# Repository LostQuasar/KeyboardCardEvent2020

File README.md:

# Keyboard Business Card Event 2020
How to sumbit your card!

First you will want to fork this repository. Then you will want to create a subfolder with your username in the submission folder of this repository. 

IE: 

    submissions
      └───username

In that folder upload:
- 1 or more pictures of your completed build
- if using KiCad, if not upload source files for appropriate program
  - `card name`.kicad_pcb 
  - `card name`.pro 
  - `card name`.sch
- `card name`.zip (a zip of the Gerber files)
- readme.md containing info from the [template](/template/readme.md)
- an edited version of `LICENSE` containing your name or username
- please host images on imgur instead of putting them in the repo

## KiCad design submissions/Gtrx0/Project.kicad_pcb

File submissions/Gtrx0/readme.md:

Business card made by Gtrx

# Concept
A modern, sleek and usable business card with an NFC tag, QR code and the ability to open a website/copy text to clipboard once plugged into a computer.

# Description
The card uses an IC that acts as an NFC tag (M24LR04E-R) which can be scanned by any NFC compatible device. After scanning, the device opens the website (Gtrxengineering.com). The NFC tag can work without the board being powered. Once the board is plugged into a computer, one of the 2 switches can be pressed. Depending on which switch is pressed, either the website will open or the email address will be copied to clipboard. The QR code also opens the website.

The website and email aren't "real" yet :P.

Thanks for reading!

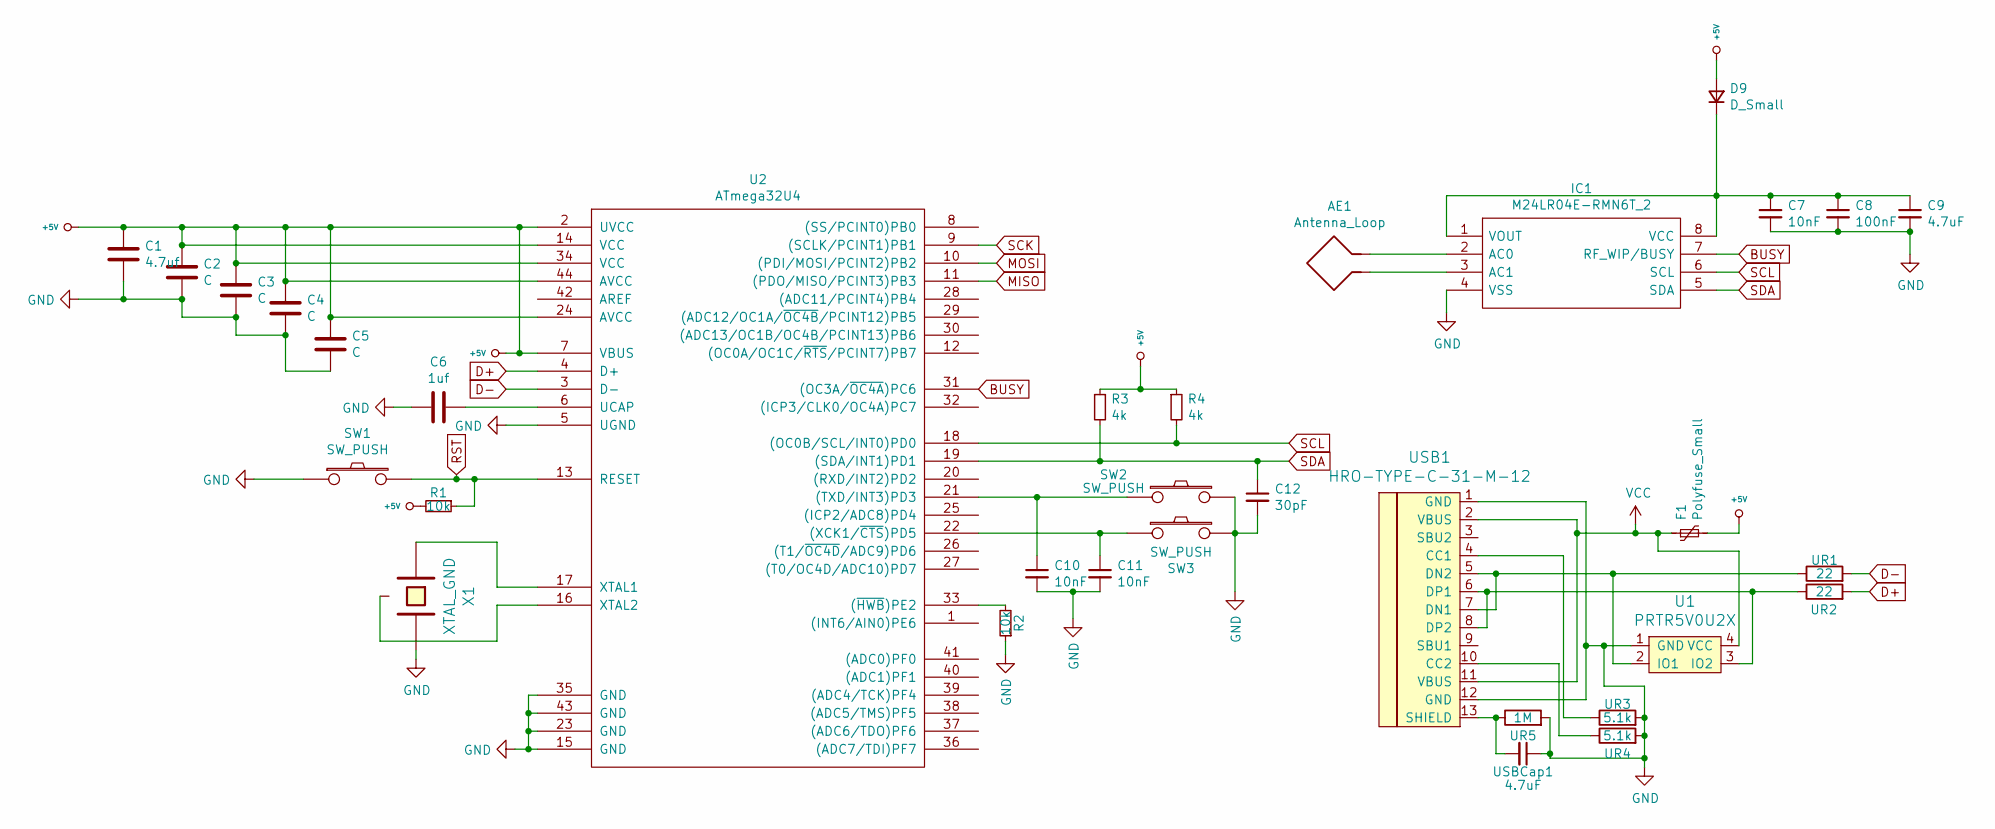
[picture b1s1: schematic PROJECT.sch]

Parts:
AE1: Antenna_Loop
C1: 4.7uf; C_0603_1608Metric
C2, C3, C4, C5: C; C_0603_1608Metric
C6: 1uf; C_0603_1608Metric
C7, C10, C11: 10nF; C_0603_1608Metric
C8: 100nF; C_0603_1608Metric
C9: 4.7uF; C_0603_1608Metric
C12: 30pF; C_0603_1608Metric
D9: D_Small; D_SOD-123
F1: Polyfuse_Small; Fuse_0805_2012Metric
IC1: M24LR04E-RMN6T_2; SOIC127P600X175-8N; Mouser Part Number 511-M24LR04E-RMN6T/2
R1, R2: 10k; R_0603_1608Metric
R3, R4: 4k; R_0603_1608Metric
SW1, SW2, SW3: SW_PUSH; SW_SPST_TL3342
U1: PRTR5V0U2X; SOT143B
U2: ATmega32U4; QFN-44-1EP_7x7mm_P0.5mm_EP5.2x5.2mm_ThermalVias
UR1, UR2: 22; R_0603_1608Metric
UR3, UR4: 5.1k; R_0603_1608Metric
UR5: 1M; R_0603_1608Metric
USB1: HRO-TYPE-C-31-M-12; HRO-TYPE-C-31-M-13
USBCap1: 4.7uF; C_0603_1608Metric
X1: XTAL_GND; CSTCE

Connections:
+5V: C1.1, C2.1, C3.1, C4.1, C5.1, D9.2 (A), F1.2, R1.2, R3.1, R4.1, U2.2 (UVCC), U2.7 (VBUS), U2.14 (VCC), U2.24 (AVCC), U2.34 (VCC), U2.44 (AVCC)
BUSY: IC1.7 (RF_WIP/BUSY), U2.31 ((OC3A/~OC4A~)PC6)
D+: U2.4 (D+), UR2.2
D-: U2.3 (D-), UR1.2
GND: C1.2, C2.2, C3.2, C4.2, C5.2, C6.2, C7.2, C8.2, C9.2, C10.2, C11.2, C12.2, IC1.4 (VSS), R2.1, SW1.1, SW2.2, SW3.2, U1.1 (GND), U2.5 (UGND), U2.15 (GND), U2.23 (GND), U2.35 (GND), U2.43 (GND), U2.45, UR3.2, UR4.2, UR5.2, USB1.1 (GND), USB1.12 (GND), USBCap1.1, X1.2; also elsewhere on the board
MISO: U2.11 ((PDO/MISO/PCINT3)PB3)
MOSI: U2.10 ((PDI/MOSI/PCINT2)PB2)
unnamed: AE1.1, AE1.2, IC1.2 (AC0), IC1.3 (AC1)
unnamed: C6.1, U2.6 (UCAP)
unnamed: C7.1, C8.1, C9.1, D9.1 (K), IC1.1 (VOUT), IC1.8 (VCC)
unnamed: C10.1, SW2.1, U2.21 ((TXD/INT3)PD3)
unnamed: C11.1, SW3.1, U2.22 ((XCK1/~CTS~)PD5)
unnamed: R2.2, U2.33 ((~HWB~)PE2)
unnamed: U1.2 (IO1), UR1.1, USB1.5 (DN2), USB1.7 (DN1)
unnamed: U1.3 (IO2), UR2.1, USB1.6 (DP1), USB1.8 (DP2)
unnamed: U2.16 (XTAL2), X1.3
unnamed: U2.17 (XTAL1), X1.1
unnamed: UR3.1, USB1.4 (CC1)
unnamed: UR4.1, USB1.10 (CC2)
unnamed 37: UR5.1, USB1.13 (SHIELD), USBCap1.2; also elsewhere on the board
RST: R1.1, SW1.2, U2.13 (RESET); also elsewhere on the board
SCK: U2.9 ((SCLK/PCINT1)PB1)
SCL: IC1.6 (SCL), R4.2, U2.18 ((OC0B/SCL/INT0)PD0)
SDA: C12.1, IC1.5 (SDA), R3.2, U2.19 ((SDA/INT1)PD1)
VCC: F1.1, U1.4 (VCC), USB1.2 (VBUS), USB1.11 (VBUS)

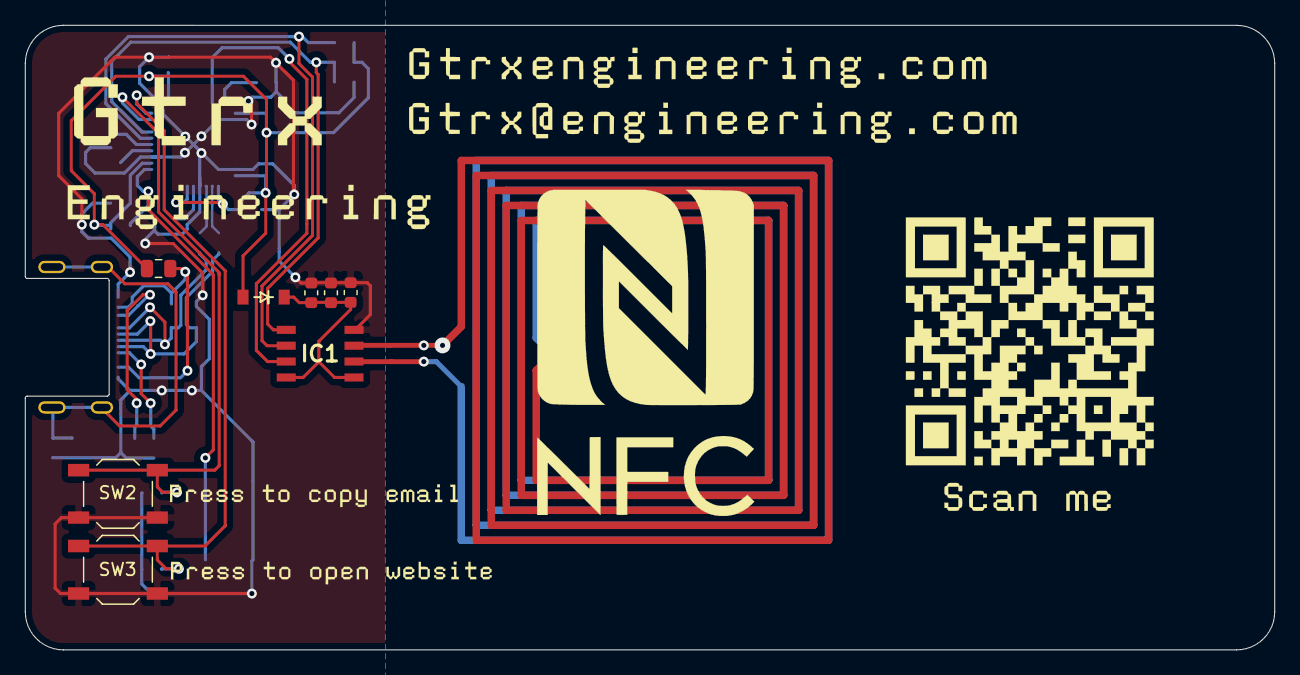
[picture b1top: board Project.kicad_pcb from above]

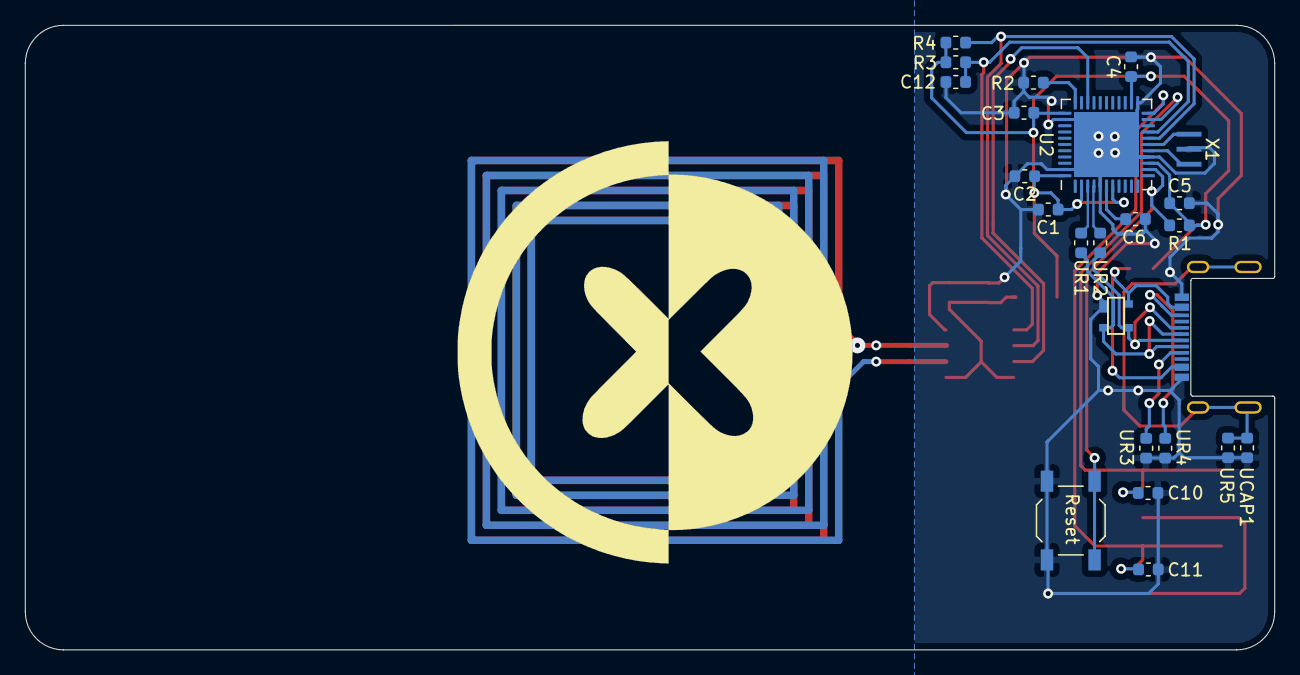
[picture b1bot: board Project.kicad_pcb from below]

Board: 2 copper layers, 100.0 x 50.0 mm, 32 parts (24 on the bottom side), 22 nets.

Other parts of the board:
Reset: SW_PUSH; SW_SPST_TL3342
UCAP1: 4.7uF; C_0603_1608Metric

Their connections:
GND: Reset.1, UCAP1.1; also elsewhere on the board
unnamed 37: UCAP1.2; also elsewhere on the board
RST: Reset.2; also elsewhere on the board

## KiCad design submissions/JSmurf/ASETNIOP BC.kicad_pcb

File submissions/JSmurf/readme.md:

# JSmurf's Business Card

## [Currently Untitled Keyboard]

[Currently Untitled Keyboard] is a one-handed ASETNIOP keyboard that is designed to be a fully-featured keyboard.

(More information to follow as development continues.)

## Parts list

- 1x ATMEGA32U4 Microcontroller
- 1x Crystal, 16MHz
- 1x Mini-B USB Connector Molex-0548190589
- 1x Low Profile Tactile Switch
- 2x Resistor, 22ohm SMD 0805
- 2x Resistor, 10k SMD 0805
- 1x Capacitor, 1uF SMD 0805
- 1x Capacitor, 10uF SMD 0805
- 3x Capacitor, 0.1uF SMD 0805
- 2x Capacitor, 22pF SMD 0805
- 10x Diode, SMD SOD-123
- 1x Polyfuse, 500mA hold, 1A trip
- 10x MX Keyswitches of your choice

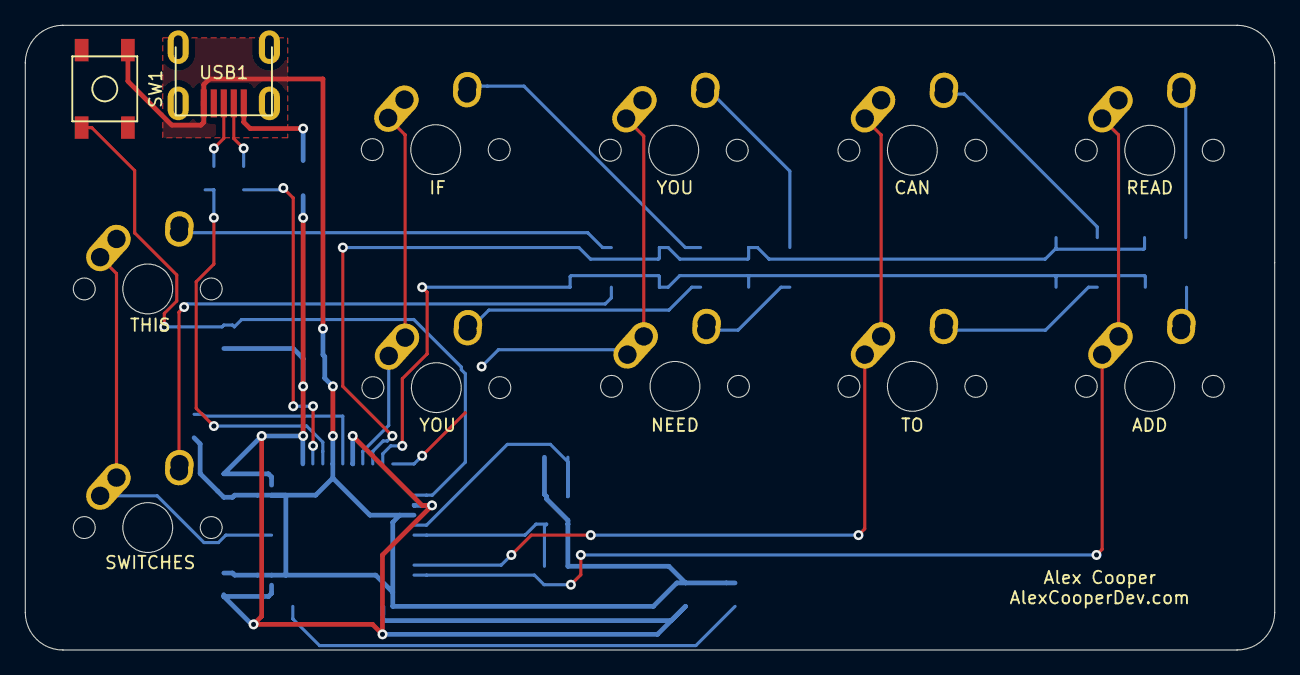
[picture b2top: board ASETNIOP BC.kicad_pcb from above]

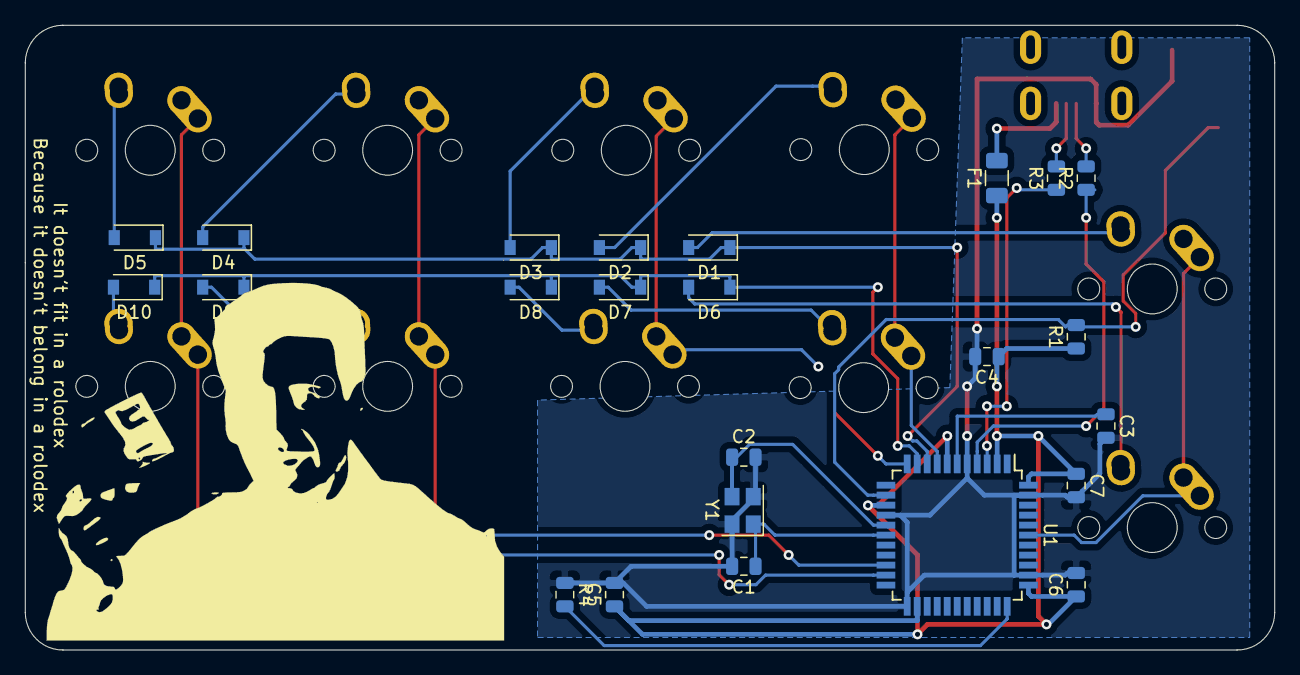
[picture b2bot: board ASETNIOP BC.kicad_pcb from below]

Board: 2 copper layers, 100.0 x 50.0 mm, 36 parts (24 on the bottom side), 29 nets.

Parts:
C1, C2: 22pF; C_0805_2012Metric
C3: 1uF; C_0805_2012Metric
C4, C5, C6: 0.1uF; C_0805_2012Metric
C7: 10uF; C_0805_2012Metric
D1, D2, D3, D4, D5, D6, D7, D8, D9, D10: SOD-123; D_SOD-123
F1: 500mA; Fuse_1206_3216Metric
MX1, MX2, MX3, MX4, MX5, MX6, MX7, MX8, MX9, MX10: MX-NoLED; MX-1U-NoLED
R1, R4: 10k; R_0805_2012Metric
R2, R3: 22; R_0805_2012Metric
SW1: SW_Push; SKQG-1155865
U1: ATmega32U4-AU; TQFP-44_10x10mm_P0.8mm
USB1: Molex-0548190589
Y1: 16MHz; Crystal_SMD_3225-4Pin_3.2x2.5mm

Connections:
+5V: C4.1, C5.1, C6.1, C7.1, F1.1, R1.1, U1.2, U1.7, U1.14, U1.24, U1.34, U1.44
COL0: MX1.1, MX6.1, U1.39
COL1: MX2.1, MX7.1, U1.8
COL2: MX3.1, MX8.1, U1.11
COL3: MX4.1, MX9.1, U1.20
COL4: MX5.1, MX10.1, U1.21
D+: R2.2, USB1.3
D-: R3.2, USB1.4
GND: C1.2, C2.2, C3.2, C4.2, C5.2, C6.2, C7.2, R4.1, SW1.1, U1.5, U1.15, U1.23, U1.35, U1.43, USB1.1, Y1.2, Y1.4
unnamed: C1.1, U1.17, Y1.1
unnamed: C2.1, U1.16, Y1.3
unnamed: C3.1, U1.6
unnamed: D1.2, MX1.2
unnamed: D2.2, MX2.2
unnamed: D3.2, MX3.2
unnamed: D4.2, MX4.2
unnamed: D5.2, MX5.2
unnamed: D6.2, MX6.2
unnamed: D7.2, MX7.2
unnamed: D8.2, MX8.2
unnamed: D9.2, MX9.2
unnamed: D10.2, MX10.2
unnamed: R1.2, SW1.2, U1.13
unnamed: R2.1, U1.4
unnamed: R3.1, U1.3
unnamed: R4.2, U1.33
ROW0: D1.1, D2.1, D3.1, D4.1, D5.1, U1.9
ROW1: D6.1, D7.1, D8.1, D9.1, D10.1, U1.10
VCC: F1.2, USB1.5

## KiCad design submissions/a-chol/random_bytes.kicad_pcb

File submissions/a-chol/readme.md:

# random_bytes' Business card

Here is a business card which functionality is related to my username.

The feature of the card is to generate random outputs where the source of randomness is a hardware random number generator, just by pressing the capacitive touch area on the card.

The hardware random number generator is based on [the following article](https://makezine.com/projects/really-really-random-number-generator/) with its implementation in the RAND frame on the card.

For this to work, I needed a 18V power source, so I implemented a 5V to 18V step up in the POWER frame.

The DIP switches let the user chose between different output formats, which could be 8bit integer, floating point value, alphanumeric keystrokes, mouse pointer displacement, ...

The USB-C port is a concept experiment where the connector plate of a USB-C receptacle is built in the PCB. If the PCB is printed with 0.6mm width, this could work.

I have no idea if it works!

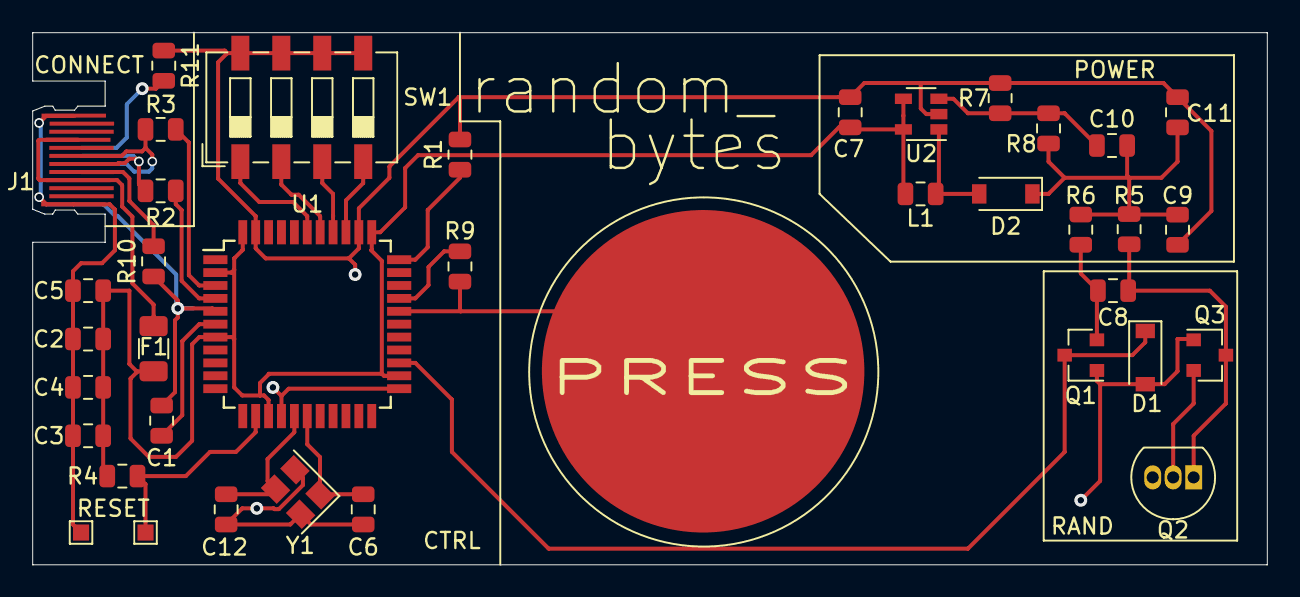
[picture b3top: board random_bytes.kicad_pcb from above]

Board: 2 copper layers, 76.6 x 33.0 mm, 38 parts (0 on the bottom side), 27 nets.

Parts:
C1: 1uF; C_0805_2012Metric
C2, C3, C4: 0.1uF; C_0805_2012Metric
C5: 10uF; C_0805_2012Metric
C6, C10, C12: 22pF; C_0805_2012Metric
C7: 4.7µF; C_0805_2012Metric
C8, C9: 0.01uF; C_0805_2012Metric
C11: 1µF; C_0805_2012Metric
CapSensor1: Capacitive_circular_pad
D1: D_Zener_Small; D_SOD-123
D2: D_Schottky; D_SOD-123
F1: Polyfuse_Small; Fuse_1206_3216Metric
GND_Pad1: TestPoint; TestPoint_Pad_1.0x1.0mm
J1: USB_C_Receptacle; USB-C_onboard_pins
L1: 10µH; L_0805_2012Metric
Q1, Q3: MMBT3904; SOT-23
Q2: 2N3904; TO-92_Inline
R1, R4: 10k; R_0805_2012Metric
R2, R3: 22; R_0805_2012Metric
R5: 4.7k; R_0805_2012Metric
R6, R9: 1M; R_0805_2012Metric
R7: 160k; R_0805_2012Metric
R8: 2.2M; R_0805_2012Metric
R10, R11: 5.1k; R_0805_2012Metric
RST_Pad1: TestPoint; TestPoint_Pad_1.0x1.0mm
SW1: SW_DIP_x04; SW_DIP_SPSTx04_Slide_6.7x11.72mm_W6.73mm_P2.54mm_LowProfile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
U1: ATmega32U4-AU; TQFP-44_10x10mm_P0.8mm
U2: TPS61041DBV; SOT-23-5
Y1: 16MHz; Crystal_SMD_3225-4Pin_3.2x2.5mm

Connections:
18V: C9.2, C10.2, C11.2, D2.1, R5.2, R6.2, R8.1
+5V: C2.1, C3.1, C4.1, C5.1, C7.2, F1.1, L1.2, R4.2, U1.2, U1.7, U1.14, U1.24, U1.34, U1.44, U2.4, U2.5
CAP_POWER: CapSensor1.1, R9.1, U1.29
CAP_VAL: R9.2, U1.30
D+: J1.A6, J1.B6, R2.2
D-: J1.A7, J1.B7, R3.2
GND: C1.2, C2.2, C3.2, C4.2, C5.2, C6.2, C7.1, C9.1, C11.1, C12.2, D1.2, GND_Pad1.1, J1.A1, J1.A12, J1.B1, J1.B12, Q1.1, Q3.1, R1.2, R7.2, R10.1, R11.1, SW1.5, SW1.6, SW1.7, SW1.8, U1.5, U1.15, U1.23, U1.35, U1.43, U2.2, Y1.2, Y1.4
unnamed: C1.1, U1.6
unnamed: C6.1, U1.17, Y1.1
unnamed: C8.1, Q2.1, Q3.3, R5.1
unnamed: C8.2, Q1.2, R6.1
unnamed: C10.1, R7.1, R8.2, U2.3
unnamed: C12.1, U1.16, Y1.3
unnamed: D2.2, L1.1, U2.1
unnamed: J1.A5, R10.2
unnamed: J1.B5, R11.2
unnamed: Q2.2, Q3.2
unnamed: R1.1, U1.33
unnamed: R2.1, U1.4
unnamed: R3.1, U1.3
unnamed: R4.1, RST_Pad1.1, U1.13
unnamed: SW1.1, U1.39
unnamed: SW1.2, U1.38
unnamed: SW1.3, U1.37
unnamed: SW1.4, U1.36
RAND: D1.1, Q1.3, U1.25
VCC: F1.2, J1.A4, J1.A9, J1.B4, J1.B9

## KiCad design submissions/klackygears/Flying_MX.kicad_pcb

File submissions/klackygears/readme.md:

# klackygears's Business card

This is my first pcb design. (I followed ai03's guide. Huge thank you!) I thought it would be fun to try some things while I was learning. It has footprints for SK6812 MINI-E that I hope work. (Big thanks to Maarten for making 95% of that footprint!) It also has a fun silk screen design I made that is inspired by the old Flying Toaster screensaver.

It's a 6 key macro pad with per-key RGB and USB C connector.

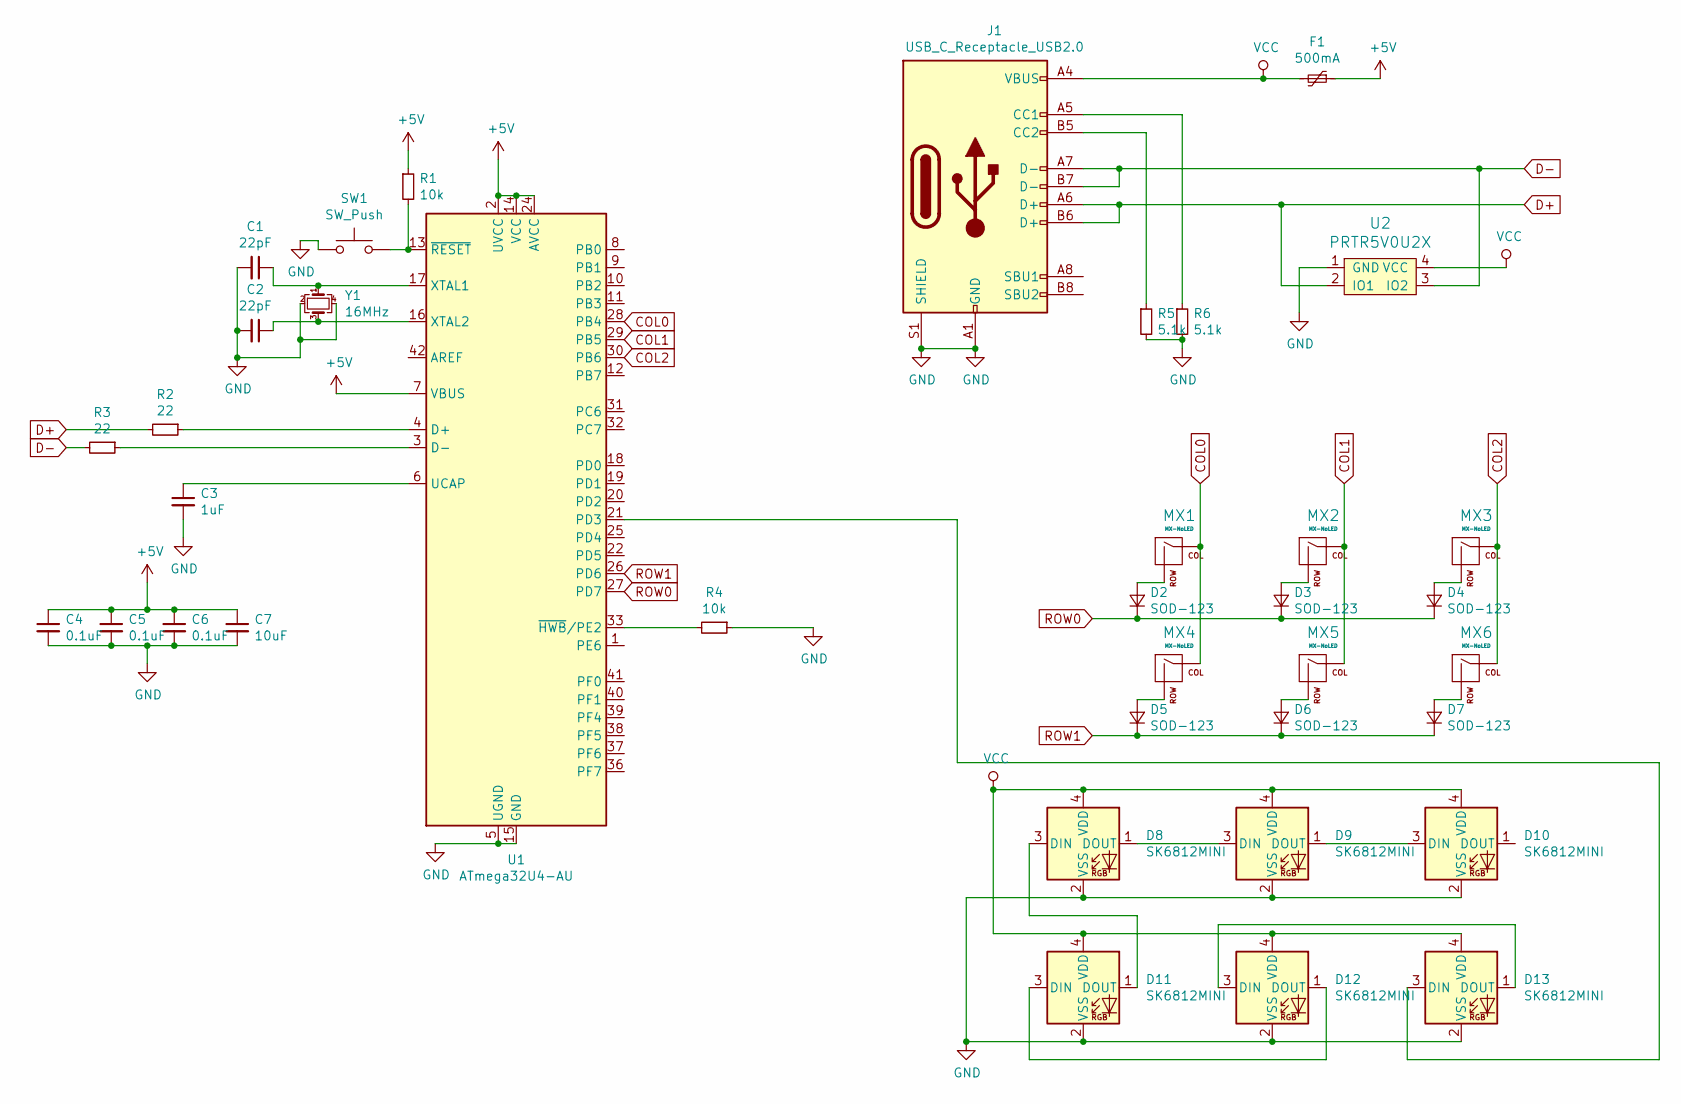
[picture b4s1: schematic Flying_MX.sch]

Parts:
C1, C2: 22pF; C_0805_2012Metric
C3: 1uF; C_0805_2012Metric
C4, C5, C6: 0.1uF; C_0805_2012Metric
C7: 10uF; C_0805_2012Metric
D2, D3, D4, D5, D6, D7: SOD-123; D_SOD-123
D8, D9, D10, D11, D12, D13: SK6812MINI; SK6812MINI-E
F1: 500mA; Fuse_1206_3216Metric
J1: USB_C_Receptacle_USB2.0; USB_C_Receptacle_GCT_USB4085
MX1, MX2, MX3, MX4, MX5, MX6: MX-NoLED; MX-ALPs-PG1350-FLIP
R1, R4: 10k; R_0805_2012Metric
R2, R3: 22; R_0805_2012Metric
R5, R6: 5.1k; R_0805_2012Metric
SW1: SW_Push; SKQG-1155865
U1: ATmega32U4-AU; TQFP-44_10x10mm_P0.8mm
U2: PRTR5V0U2X; SOT143B
Y1: 16MHz; Crystal_SMD_3225-4Pin_3.2x2.5mm

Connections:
+5V: C4.1, C5.1, C6.1, C7.1, F1.1, R1.1, U1.2 (UVCC), U1.7 (VBUS), U1.14 (VCC), U1.24 (AVCC), U1.34 (VCC), U1.44 (AVCC)
COL0: MX1.1 (COL), MX4.1 (COL), U1.28 (PB4)
COL1: MX2.1 (COL), MX5.1 (COL), U1.29 (PB5)
COL2: MX3.1 (COL), MX6.1 (COL), U1.30 (PB6)
D+: J1.A6 (D+), J1.B6 (D+), R2.2, U2.2 (IO1)
D-: J1.A7 (D-), J1.B7 (D-), R3.2, U2.3 (IO2)
GND: C1.2, C2.2, C3.2, C4.2, C5.2, C6.2, C7.2, D8.2 (VSS), D9.2 (VSS), D10.2 (VSS), D11.2 (VSS), D12.2 (VSS), D13.2 (VSS), J1.A1 (GND), J1.A12 (GND), J1.B1 (GND), J1.B12 (GND), J1.S1 (SHIELD), R4.1, R5.2, R6.2, SW1.1, U1.5 (UGND), U1.15 (GND), U1.23 (GND), U1.35 (GND), U1.43 (GND), U2.1 (GND), Y1.2, Y1.4
unnamed: C1.1, U1.17 (XTAL1), Y1.1
unnamed: C2.1, U1.16 (XTAL2), Y1.3
unnamed: C3.1, U1.6 (UCAP)
unnamed: D2.2 (A), MX1.2 (ROW)
unnamed: D3.2 (A), MX2.2 (ROW)
unnamed: D4.2 (A), MX3.2 (ROW)
unnamed: D5.2 (A), MX4.2 (ROW)
unnamed: D6.2 (A), MX5.2 (ROW)
unnamed: D7.2 (A), MX6.2 (ROW)
unnamed: D8.1 (DOUT), D9.3 (DIN)
unnamed: D9.1 (DOUT), D10.3 (DIN)
unnamed: D8.3 (DIN), D11.1 (DOUT)
unnamed: D11.3 (DIN), D12.1 (DOUT)
unnamed: D12.3 (DIN), D13.1 (DOUT)
unnamed: D13.3 (DIN), U1.21 (PD3)
unnamed: J1.A5 (CC1), R6.1
unnamed: J1.B5 (CC2), R5.1
unnamed: R1.2, SW1.2, U1.13 (~RESET)
unnamed: R2.1, U1.4 (D+)
unnamed: R3.1, U1.3 (D-)
unnamed: R4.2, U1.33 (~HWB~/PE2)
ROW0: D2.1 (K), D3.1 (K), D4.1 (K), U1.27 (PD7)
ROW1: D5.1 (K), D6.1 (K), D7.1 (K), U1.26 (PD6)
VCC: D8.4 (VDD), D9.4 (VDD), D10.4 (VDD), D11.4 (VDD), D12.4 (VDD), D13.4 (VDD), F1.2, J1.A4 (VBUS), J1.A9 (VBUS), J1.B4 (VBUS), J1.B9 (VBUS), U2.4 (VCC)

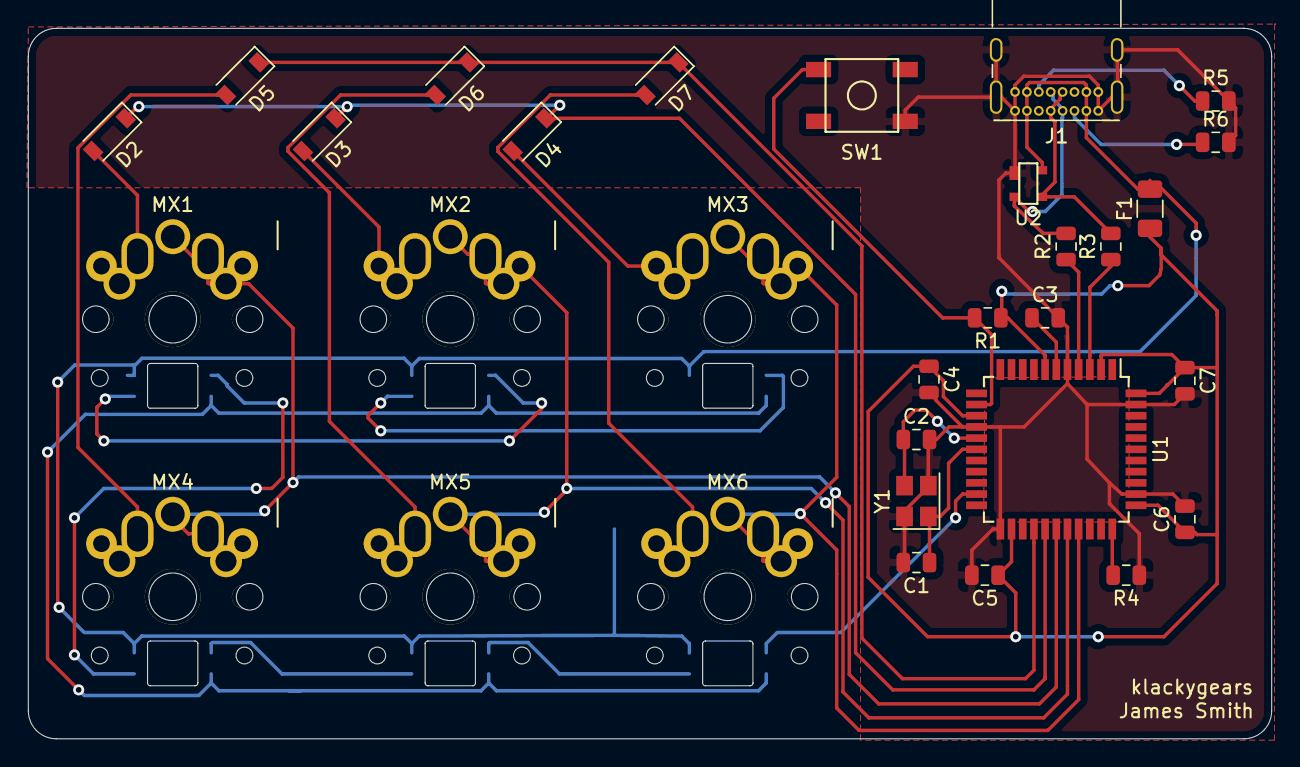
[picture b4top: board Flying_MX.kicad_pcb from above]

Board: 2 copper layers, 88.9 x 50.8 mm, 37 parts (0 on the bottom side), 31 nets.

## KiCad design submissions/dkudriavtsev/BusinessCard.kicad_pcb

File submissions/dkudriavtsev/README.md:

# dkudriavtsev's submission

This is a Planck-like keyboard in a 100x50mm form factor. It can be manufactured entirely through JLCPCB.

Features include full N-key rollover, STM32 ARM microcontroller, USB-C, ESD protection, and more.

Compatible with QMK firmware.

## Images

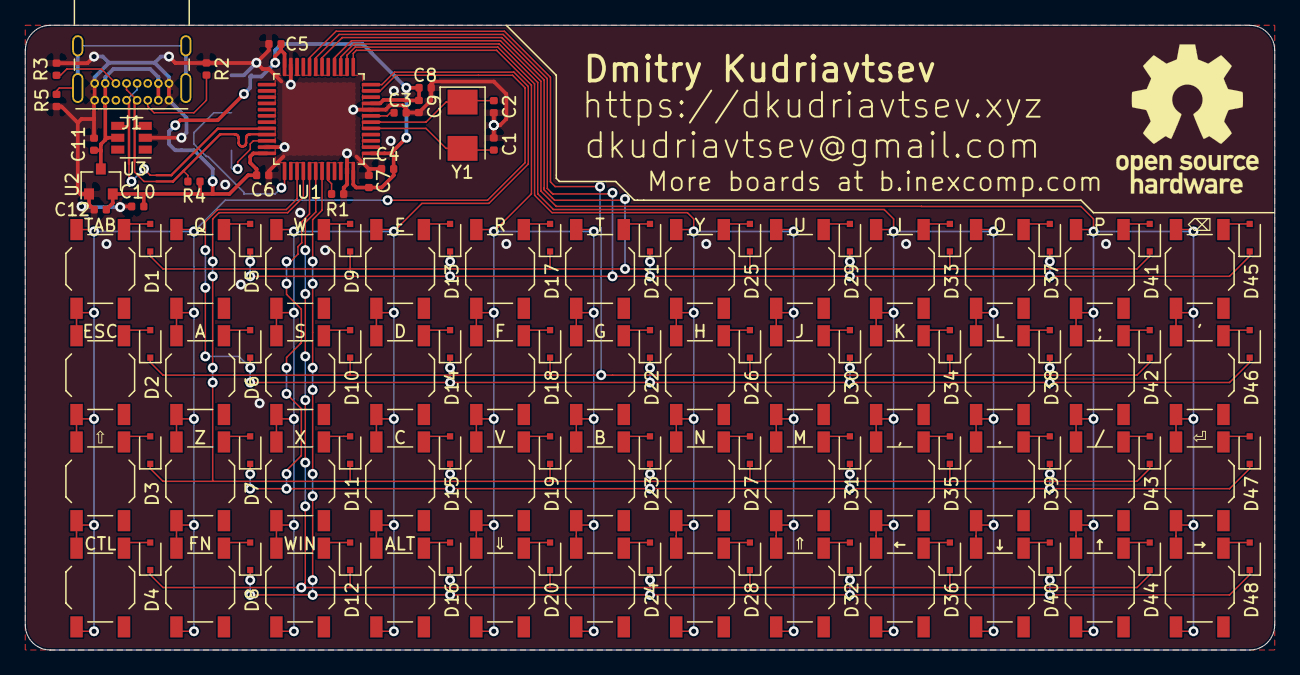
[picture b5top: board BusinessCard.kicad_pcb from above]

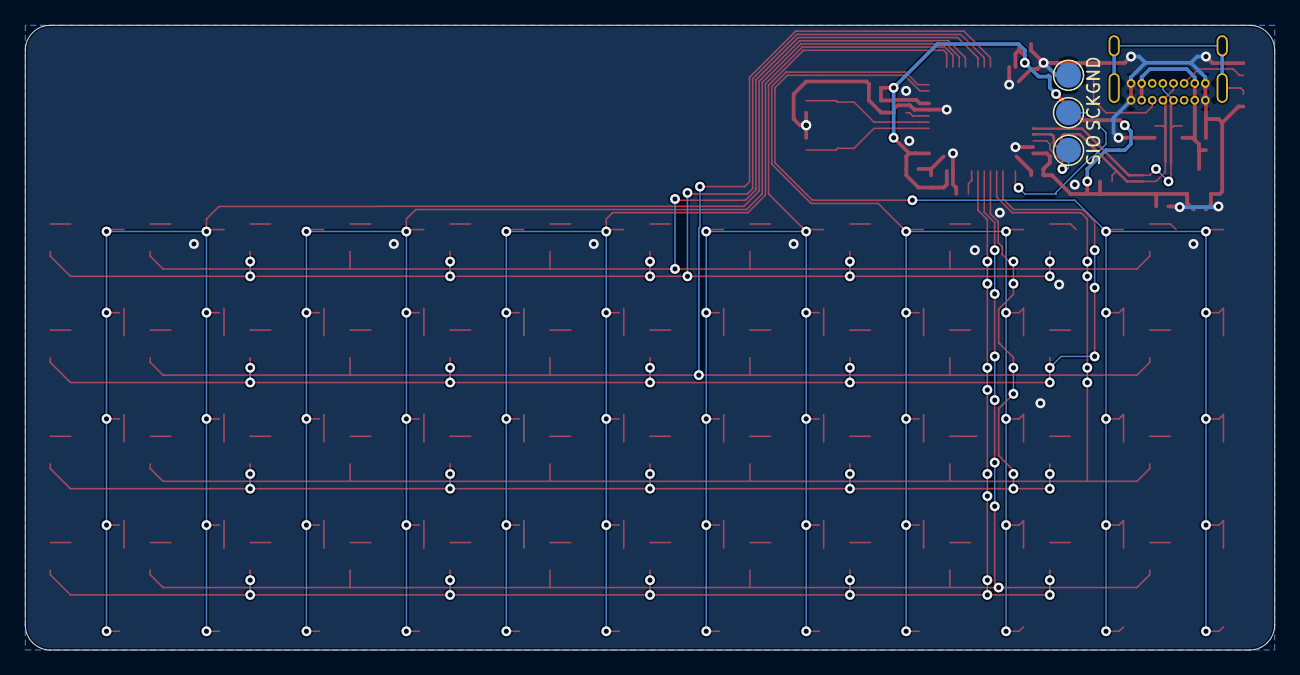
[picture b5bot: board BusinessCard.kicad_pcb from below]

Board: 2 copper layers, 100.0 x 50.0 mm, 121 parts (3 on the bottom side), 76 nets.

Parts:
C1, C2: 20pf; C_0402_1005Metric
C3, C4, C5, C6, C7, C9, C10: 100nf; C_0402_1005Metric
C8, C11, C12: 1uf; C_0402_1005Metric
D1, D2, D3, D4, D5, D6, D7, D8, D9, D10, D11, D12, D13, D14, D15, D16, D17, D18, D19, D20, D21, D22, D23, D24, D25, D26, D27, D28, D29, D30, D31, D32, D33, D34, D35, D36, D37, D38, D39, D40, D41, D42, D43, D44, D45, D46, D47, D48: D_Small; D_SOD-323F
GND1: TestPoint; TestPoint_Pad_D2.0mm
J1: USB_C_Receptacle_USB2.0; USB_C_Receptacle_GCT_USB4085
R1: 10k; R_0402_1005Metric
R2, R3: 5.1K; R_0402_1005Metric
R4: 1.5K; R_0402_1005Metric
R5: 1M; R_0402_1005Metric
SCK1: TestPoint; TestPoint_Pad_D2.0mm
SIO1: TestPoint; TestPoint_Pad_D2.0mm
SW1, SW2, SW3, SW4, SW5, SW6, SW7, SW8, SW9, SW10, SW11, SW12, SW13, SW14, SW15, SW16, SW17, SW18, SW19, SW20, SW21, SW22, SW23, SW24, SW25, SW26, SW27, SW28, SW29, SW30, SW31, SW32, SW33, SW34, SW35, SW36, SW37, SW38, SW39, SW40, SW41, SW42, SW43, SW44, SW45, SW46, SW47, SW48: SW_Push_45deg; SW_SPST_TL3342
U1: STM32F103C8Tx; LQFP-48_7x7mm_P0.5mm
U2: XC6206PxxxMR; SOT-23
U3: SRV05-4; SOT-23-6
Y1: 8MHz; Crystal_SMD_5032-2Pin_5.0x3.2mm

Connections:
+5V: C11.2, J1.A4, J1.A9, J1.B4, J1.B9, U2.3, U3.5
/MCU Support/CC1: J1.A5, R2.1
/MCU Support/CC2: J1.B5, R3.2
BOOT0: R1.1, U1.44
DA+: J1.A6, J1.B6, R4.2, U1.33, U3.3
DA-: J1.A7, J1.B7, U1.32, U3.4
GND: C1.2, C2.2, C3.2, C4.1, C5.1, C6.1, C7.1, C8.1, C9.1, C10.1, C11.1, C12.2, GND1.1, J1.A1, J1.A12, J1.B1, J1.B12, R1.2, R2.2, R3.1, R5.1, U1.8, U1.23, U1.35, U1.47, U2.1, U3.2
NRST: C3.1, U1.7
unnamed: D1.2, SW1.2
unnamed: D2.2, SW2.2
unnamed: D3.2, SW3.2
unnamed: D4.2, SW4.2
unnamed: D5.2, SW5.2
unnamed: D6.2, SW6.2
unnamed: D7.2, SW7.2
unnamed: D8.2, SW8.2
unnamed: D9.2, SW9.2
unnamed: D10.2, SW10.2
unnamed: D11.2, SW11.2
unnamed: D12.2, SW12.2
unnamed: D13.2, SW13.2
unnamed: D14.2, SW14.2
unnamed: D15.2, SW15.2
unnamed: D16.2, SW16.2
unnamed: D17.2, SW17.2
unnamed: D18.2, SW18.2
unnamed: D19.2, SW19.2
unnamed: D20.2, SW20.2
unnamed: D21.2, SW21.2
unnamed: D22.2, SW22.2
unnamed: D23.2, SW23.2
unnamed: D24.2, SW24.2
unnamed: D25.2, SW25.2
unnamed: D26.2, SW26.2
unnamed: D27.2, SW27.2
unnamed: D28.2, SW28.2
unnamed: D29.2, SW29.2
unnamed: D30.2, SW30.2
unnamed: D31.2, SW31.2
unnamed: D32.2, SW32.2
unnamed: D33.2, SW33.2
unnamed: D34.2, SW34.2
unnamed: D35.2, SW35.2
unnamed: D36.2, SW36.2
unnamed: D37.2, SW37.2
unnamed: D38.2, SW38.2
unnamed: D39.2, SW39.2
unnamed: D40.2, SW40.2
unnamed: D41.2, SW41.2
unnamed: D42.2, SW42.2
unnamed: D43.2, SW43.2
unnamed: D44.2, SW44.2
unnamed: D45.2, SW45.2
unnamed: D46.2, SW46.2
unnamed: D47.2, SW47.2
unnamed: D48.2, SW48.2
unnamed: J1.S1, R5.2
PD0: C1.1, U1.5, Y1.2
PD1: C2.1, U1.6, Y1.1
SWDCLK: SCK1.1, U1.37
SWDIO: SIO1.1, U1.34
VBAT: C4.2, C5.2, C6.2, C7.2, C8.2, C9.2, C10.2, C12.1, R4.1, U1.1, U1.9, U1.24, U1.36, U1.48, U2.2
col1: SW1.1, SW2.1, SW3.1, SW4.1, SW5.1, SW6.1, SW7.1, SW8.1, U1.11
col2: SW9.1, SW10.1, SW11.1, SW12.1, SW13.1, SW14.1, SW15.1, SW16.1, U1.12
col3: SW17.1, SW18.1, SW19.1, SW20.1, SW21.1, SW22.1, SW23.1, SW24.1, U1.13
col4: SW25.1, SW26.1, SW27.1, SW28.1, SW29.1, SW30.1, SW31.1, SW32.1, U1.14
col5: SW33.1, SW34.1, SW35.1, SW36.1, SW37.1, SW38.1, SW39.1, SW40.1, U1.15
col6: SW41.1, SW42.1, SW43.1, SW44.1, SW45.1, SW46.1, SW47.1, SW48.1, U1.16
row0: D1.1, D9.1, D17.1, D25.1, D33.1, D41.1, U1.18
row1: D5.1, D13.1, D21.1, D29.1, D37.1, D45.1, U1.19
row2: D2.1, D10.1, D18.1, D26.1, D34.1, D42.1, U1.20
row3: D6.1, D14.1, D22.1, D30.1, D38.1, D46.1, U1.39
row4: D3.1, D11.1, D19.1, D27.1, D35.1, D43.1, U1.40
row5: D7.1, D15.1, D23.1, D31.1, D39.1, D47.1, U1.41
row6: D4.1, D12.1, D20.1, D28.1, D36.1, D44.1, U1.42
row7: D8.1, D16.1, D24.1, D32.1, D40.1, D48.1, U1.43

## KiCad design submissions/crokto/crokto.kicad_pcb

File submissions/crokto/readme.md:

#Business Card 60%
by Crokto

##Concept
A fully functional keyboard, almost entirely assembled by JLCPCB, only requiring the USB port to be added on. This combination of low per-unit price and effort allows it to be given away freely without much cost, as with a business card.

Meant to be operated while held in hand, serving as something in-between a phone's touchscreen keyboard and a full desktop keyboard.

Created a (mostly fictional) website to go with the business card.

JLC gerber & PCBA files are included, all that's needed is to solder on an HRO-TYPE-C-31-M-13 connector - can use this video as reference on soldering this type of connector https://www.youtube.com/watch?v=3IOdTOevj2k

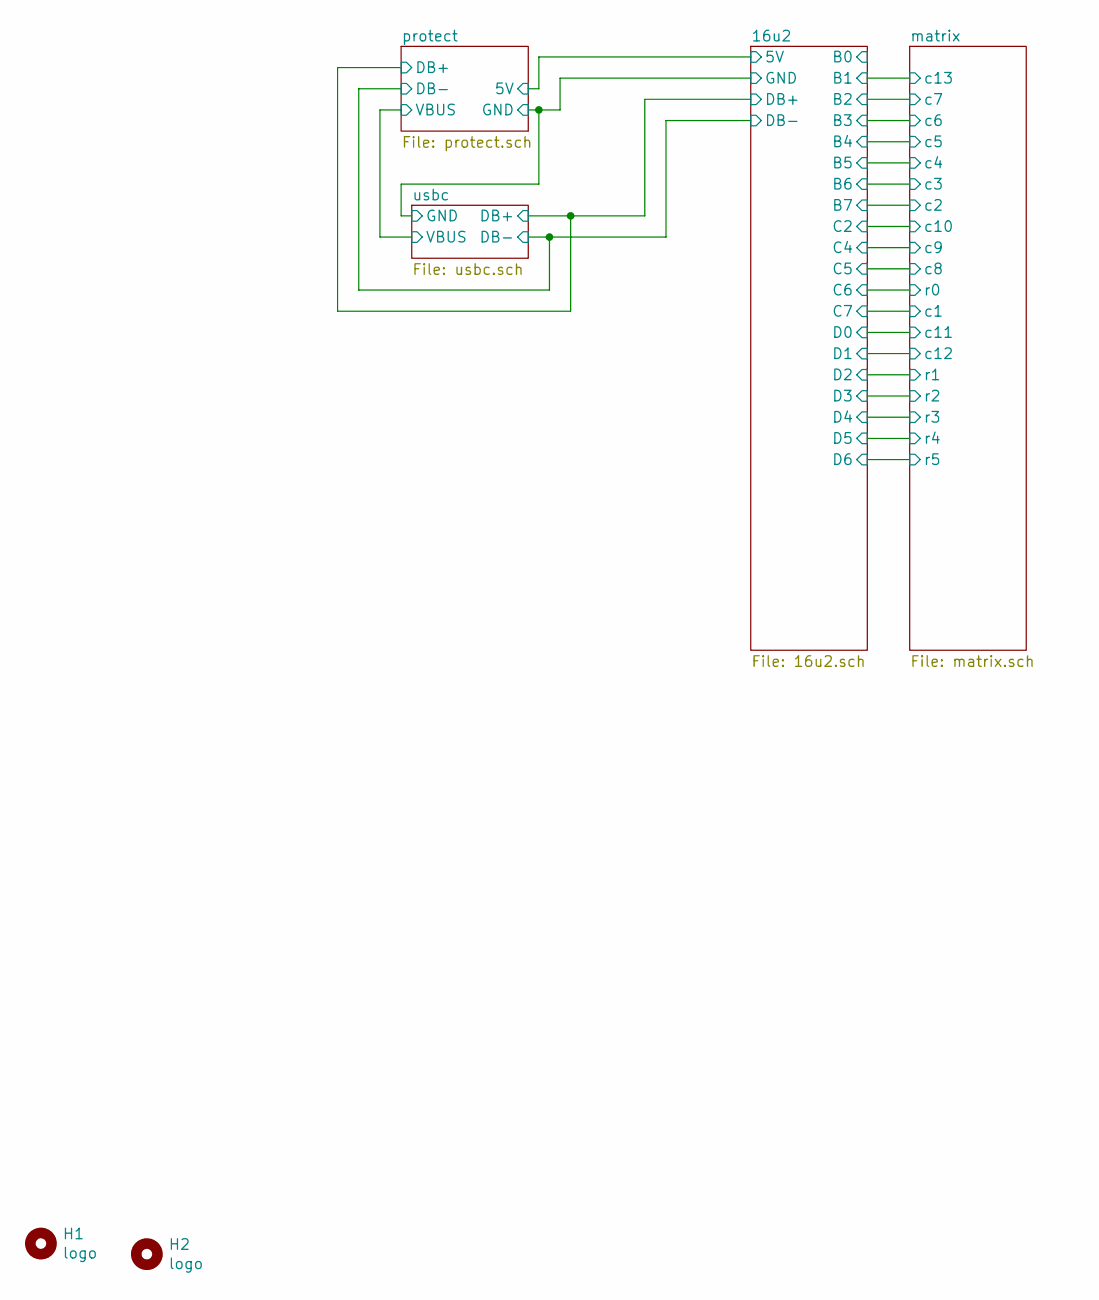
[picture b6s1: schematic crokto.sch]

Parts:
H1: logo; 100mm wide logo
H2: logo; qr

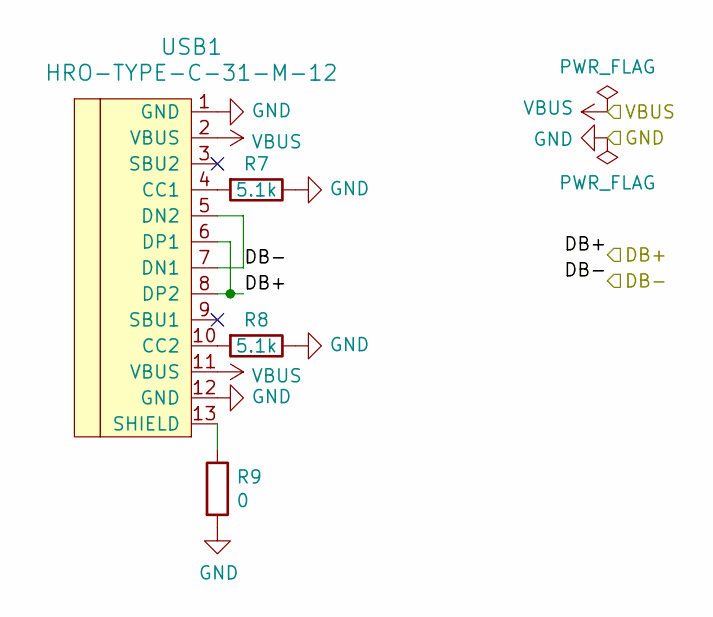
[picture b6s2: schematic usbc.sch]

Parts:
R7, R8: 5.1k; R_0402_1005Metric; lcsc C25905
R9: 0; R_0402_1005Metric; lcsc C25905
USB1: HRO-TYPE-C-31-M-12; HRO-TYPE-C-31-M-13

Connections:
/16u2/DB+: USB1.6 (DP1), USB1.8 (DP2); also elsewhere on the board
/16u2/DB-: USB1.5 (DN2), USB1.7 (DN1); also elsewhere on the board
GND: R7.1, R8.1, R9.2, USB1.1 (GND), USB1.12 (GND); also elsewhere on the board
unnamed: R7.2, USB1.4 (CC1)
unnamed: R8.2, USB1.10 (CC2)
unnamed: R9.1, USB1.13 (SHIELD)
VBUS: USB1.2 (VBUS), USB1.11 (VBUS); also elsewhere on the board

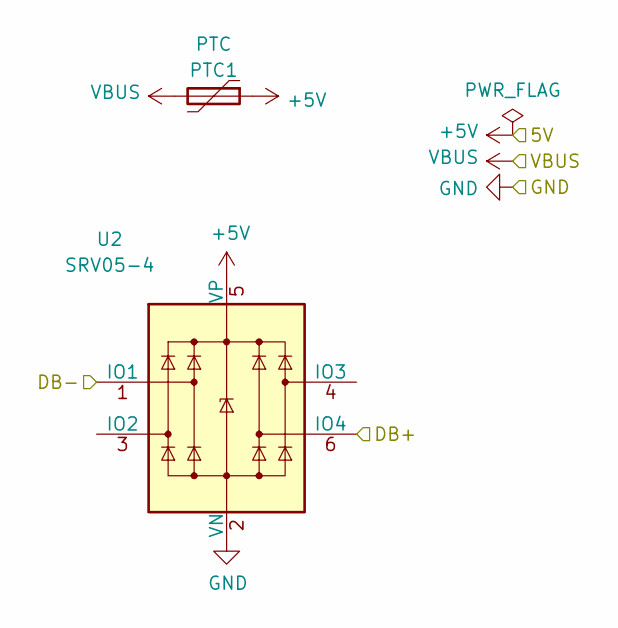
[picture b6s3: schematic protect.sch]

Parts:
PTC1: PTC; Fuse_1206_3216Metric; lcsc C70076
U2: SRV05-4; SOT-23-6; lcsc C85364

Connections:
+5V: PTC1.1, U2.5 (VP); also elsewhere on the board
/16u2/DB+: U2.6 (IO4); also elsewhere on the board
/16u2/DB-: U2.1 (IO1); also elsewhere on the board
GND: U2.2 (VN); also elsewhere on the board
VBUS: PTC1.2; also elsewhere on the board
